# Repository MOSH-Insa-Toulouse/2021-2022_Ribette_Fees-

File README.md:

# 2021-2022_Ribette_Fees-
Projet capteur INSA Toulouse 2021-2022

# Sommaire
[1. A propos du projet](#A_propos)

[2. Circuit électronique](#Circuit_elec)

[3. Schématique et PCB KiCad](#Schem)

[4. Code Arduino](#Code)

[5. Application APK Bluetooth](#App)

[6. Banc de test](Banc)

[7. Datasheet](Sheet)

# 1. A propos du projet 

Ce répertoire comporte les différentes étapes effectuées pour le projet de l'UF "Du capteur au banc de test en open source hardware" proposé en 4ème année de Génie Physique de l'INSA Toulouse. Ce travail a été effectué par Antoine Fées et Mathis Ribette, sous la direction de M. Jérémie Grisolia, et avec l'aide de M. Biganzoli et Mme Crouzet, de l'INSA Toulouse. 

## 1.1 Prémices 

Les prémices de ce travail viennent d'un article scientifique,  _Pencil Drawn Strain Gauges and Chemiresistors on Paper, by Cheng-Wei Lin, Zhibo Zhao, Jaemyung Kim & Jiaxing Huang, Nature, published on January 22, 2014_ [1](https://www.nature.com/articles/srep03812), dans lequel est fabriqué un capteur de déformation à base d'une feuille de papier et d'un crayon à papier, avec une mine en graphite.. Le système granulaire que composent les particules de graphite étalées sur une feuille de papier par un crayon se comporte d'une manière intéressante : lorsque le papier est courbé, les particules de graphite se rapprochent ou s'éloignent, induisant une diminution ou une augmentation de la résistivité globale du "circuit électrique" ainsi créé. 

La grande difficulté vient de la résistivité de ce système, particulièrement élevée. Lorsqu'il est mélangé avec des molécules liantes pour qu'il soit moins friable, sa résistivité augmente fortement. Les crayons dans le commerce, des XB aux XH en passant par le standard HB, B pour les plus gras (bold) et H pour les plus durs (hard), avec X le niveau de gras ou de dureté associé (un 4B sera plus gras qu'un 2B et un 4H plus dur qu'un 2H), seront ceux que nous utiliserons. Dans cette classification, les plus gras comportent le plus de graphite et les plus durs le plus de molécules liantes. 
Cette différence de composition chimique et donc de dureté, est mise en évidence dans l'article par EDS _(energy dispersive spectroscopy)_, où les résultats suivants sont obtenus : 
- Plus on se rapproche du 9H, plus la proportion de liant est élevée. Les principaux éléments sont alors métalliques (Mg, Al) ou pseudo-métalliques (Si), avec également une forte teneur en oxygène. 
- A l'inverse, plus on se rapproche du 9B, plus la concentration en carbone augmente et plus celle des liants diminue.  

_Image ci-dessus : figure 2 de l'article : (a) EDS spectra of pencil leads correlating hardness with the fraction of carbon. Intensities of all of the spectra were normalized based on the carbon peak. (b–g) Optical microscopy images of traces drawn on the paper substrates from pencils of decreasing hardness._[1](https://www.nature.com/articles/srep03812)

## 1.2 Jauge de contrainte et graphite 

L'équipe de chercheurs a par la suite utilisé ces différents crayons et tracé des jauges de contraintes en forme de U sur des feuilles de papier. Ces jauges présentent une longueur de trait d'environ quelques centimètres pour une largeur de trait de quelques millimètres, comme le montre la figure 3 (a) de l'article ci-dessous. 
Le mécanisme de rapprochement ou d'éloignement des différents grains du système granulaire y est également représenté, (b-c-d).

_Image ci-dessus : figure 3 de l'article : (a) A photograph showing the U-shaped pencil trace drawn on a paper beam functioning as a strain gauge. (b) Schematic drawing shows that the number of connected graphite particle chains varies depending on the types of deformation. (c–d) Photograph of the gauge deformed by a single finger in compression and tension, respectively._[1](https://www.nature.com/articles/srep03812)

Les résistances obtenues sur ces dimensions par l'équipe de chercheurs sont alors les suivantes : 

| Crayon utilisé      | Résistance obtenue| 
| ------------- |:-------------:| 
| 9B     | 200 kOhms | 
| 6B     | 500 kOhms     | 
| 2B | 2 MOhms     |  
| HB | 20 MOhms |

Notons que l'article soutient que les résistances supérieures à 20 MOhms n'ont pas pu etre mesurées par l'équipe (un multimètre a été utilisé). Nous proposons alors de fabriquer un circuit électronique permettant de mesurer la variation de résistance relative à la déformation, afin d'obtenir un _flex sensor_ low-tech, open source et _user-friendly_. 

# 2. Circuit électronique 

Le circuit électronique que nous avons utilisé est un montage amplificateur à transimpédance, à amplificateur opérationnel. Afin de garantir une facilité d'utilisation, nous avons également ajouté un module Bluetooth qui nous permet, via une application réalisé avec le _MIT App Inventor_ de communiquer avec un téléphone portable android. Un potentiomètre digital commandé en SPI, monté en mode rhéostat à la place d'une résistance, nous permet de modifier le gain de l'amplificateur en temps réel. Nous avons également intégré un encodeur rotatoire, qui permet à l'utilisateur de faire des modifications en temps réel des actions du circuit, ainsi qu'un écran OLED qui affiche des informations utiles à l'utilisateur. Ce circuit électronique est monté sur PCB, puis monté sur un microcontroleur Arduino UNO. 

## 2.1 Choix du matériel 

Liste du matériel : 

| Fonction     | Référence| 
| ------------- |:-------------:| 
| Microcontroleur | Arduino UNO |
| Amplificateur opérationnel à faible bruit     | LTC 1050 | 
| Module Bluetooth     | HC05    | 
| Module encodeur rotatoire  | KY-040-GT055     | 
| Potentiomètre digital | MCP41050 |
| Résistances | 270k, 100k, 10k, 33 ohms ...|
| Capacités | 100pF, 10uF ...|

## 2.2 Schématisation du circuit électronique et modifications apportées

Une représentation 3D de notre PCB est visualisable sur les images ci-dessous, issues du logiciel Kicad : 

Un schéma LTSpice du matériel est visible sur l'image ci-dessous, qui est fidèle au circuit tel que fabriqué sur le PCB. Par la suite cependant, nous introduirons plusieurs manières différentes de représenter notre _flex sensor_, notamment afin de tester l'impact du bruit :

La résistance {Rsensor} étant le _flex sensor_ et la résistance Rvar étant le potentiomètre digital, monté en série avec une résistance de 33 Ohms. La sortie Vout est reliée à une entrée analogique du CAN du microcontroleur arduino, qui traitera la donnée analogique brute afin d'en extraire des informations. 
Une analyse électrique du schéma précédent donne : 

- V+ = E*(R1//C1)/(Rsens+R5+(R1//C1))
- V- = Vout/(1+((R3//C4)+R6)/(R2+Rvar))
- **Vout = E(R1//C1)(1+((R3//C4)+R6)/(R2+Rvar))/(Rsens+R5+(R1//C1)**
, où E=5V. 

On remarque que :

• R5 en entrée protège l'ampli opérationnel contre les décharges électrostatiques, et
forme avec C1 un filtre pour les bruits en tension
• C1 et R1 forment un filtre pour le bruit en courant
• R2 est adaptable avec le potentiomètre digital, pour changer le calibre
• C4 et R3 forment un filtre actif
• C2 et R6 forment le filtre de sortie
• C3 filtre le bruit d'alimentation

Dans notre cas, la seule modification permanente est l'ajout d'un potentiomètre digital dont la résistance varie entre 500 Ohms et 51800 Ohms environ, et le remplacement de R3 par une résistance plus élevée (270 kOhms) afin d'augmenter le gain possible par notre montage. En effet, comme nous l'avons vu avec la formule précedente, la tension de sortie est à peu près proportionnelle à 1+R3/Rvar et donc augmenter R3 nous permet d'augmenter le gain. Le potentiomètre digital est commandé sur 8 bits et donc peut prendre 256 valeurs de résistance régulièrement espacées, environ de 200 Ohms les unes des autres. Le milieu de cette plage de fonctionnement étant environ à 25 kOhms, nous avons décidé d'augmenter R3 afin d'avoir, en conditions "nominales" un gain d'environ 11. Rappelons que le gain conseillé était de 100. Il nous est possible d'arriver à cette valeur de gain, mais il faut pour cela imposer une résistance d'environ 2,7kOhms au potentiomètre digital, ce qui n'arrive qu'à environ le dixième de sa plage utilsable. Une solution, afin de toujours repousser les limites de ce gain, est d'augmenter la valeur de R3 et diminuer celle de Rvar, mais on se heuret à d'autre problèmes rencontrés lorsque les résistances sont très élevées.  

Une autre solution, plus couteuse, serait d'adjoindre un étage amplificateur inverseur à la suite d'un amplificateur transimpédance : nous n'aurions pas besoin de résistances élevées. 

## 2.3 Test de la validité du modèle électrique 

Testons notre formule pour le gain. En utilisant la formule **Vout = E(R1//C1)(1+((R3//C4)+R6)/(R2+Rvar))/(Rsens+R5+(R1//C1)** sur excel, on obtient : 

De l'autre coté, une analyse effectuée de la meme manière avec le logiciel spice donne la courbe ci-dessous, où on voit la tension de sortie Vout en fonction de la résistance du capteur pour différentes valeurs de résistance imposées par le potentiomètre digital. 

Où les instructions données sont : 
- **.step param Rvar 1k 51k 10k**
- **.step param Rsensor 1000k 20000k 1000k**
- **.op**

Ces instructions ordonnent au logiciel SPICE de calculer l'**operating point**, le point d'équilibre du circuit et sa valeur de tension de sortie associée. Nous remarquons les memes courbes que pour le calcul excel : la fonction de transfert écrite ci-dessus semble correcte. Au-delà de cela, on remarque que des valeurs précises de résistances imposées par le potentiomètre digital sont nécessaires pour garder la tension de sortie *Vout* dans une fourchette facilement utilisable par l'entrée analogique du microcontroleur arduino. Nous verrons plus tard qu'une solution de réglage automatique du gain a été mise en oeuvre et testée, et les résultats qu'elle produit. 
Nous remarquons que les variations de tensions de sortie ne répondent pas linéairement aux variations de résistance du capteur. En particulier, deux problèmes se posent : 

- Pour des résistances faibles et des gains forts, la tension de sortie dépasse rapidement les 5V et le capteur sature. Cet effet devient prégnant pour des résistances de valeurs faibles (inférieures au MOhm) et la résistance du potentiomètre digital faible également. Un réglage du potentiomètre digital à de très grandes valeurs de résistance permet de contourner ce problème en diminuant le gain. 
- Pour des résistances de capteur élevées et des gains forts, on remarque un aplatissement de la courbe, *i.e.* une variation importante de résistance du capteur (une déformation importante) s'accompagne d'une variation faible de tension de sortie Vout. Cela pose un problème du à la mesurabilité d'une variation de tension, qui n'est pas assurée pour des variations faibles. Rappelons que le quantum de variation pour un microcontroleur Arduino UNO avec un *CAN* de 10bits est d'environ 5mV (5mV/2^10 = 4,88 mV). Des variations inférieures à 5mV ne sont donc pas mesurables, d'autant plus que du bruit apparait et augmente encore la difficulté de la mesure. 
- Un troisème problème est celui de la précision du potentiomètre digital. Un bref calcul indique que 200 ohms d'écart entre deux valeurs de Rvar impose une différence de G = (1+(R3+R6)/(R2+Rvar)) de 0,09 environ à Rvar = 25k, et 8,09 environ à Rvar = 2,5k, soit respectivement 0,74% et 7,8% du gain. Cette différence n'est pas négligeable et doit etre prise en compte lors de la détermination de la mesure. En somme, on essaiera au maximum de se placer dans une zone où cette différence à le moins d'impact, donc à des gains plus faibles. 

1) Conditions nominales d'utilisation. 

En somme, **plus la résistance du capteur augmente, plus ses variations deviennent difficiles à mesurer**. Ces éléments nous permettent de répondre à la première question, celle de tester les **conditions nominales** du capteur. 
Afin de garantir une mesure plus ou moins précise, la condition nominale d'utilisation du capteur sera dans une plage de résistannces de **1 à 10 MOhms** environ. Au-delà, il deviendra impossible d'ajuster en temps réel la valeur du potentiomètre digital avec suffisamment de précision pour ne pas compromettre la mesure. Il sera donc nécessaire de fixer sa valeur. La limite sera alors les 5mV de quantum de variation détectable par l'Arduino, et évidemment, le bruit qui subsistera. 
Un test empirique sur des résistances connues, de 1 et 10 MOhm, nous a permis de nous convaincre de la précision de la mesure, et de raisonnablement croire à la validité de cette plage de résistances. 

2) Influence de l'*offset voltage* imposé par l'amplificateur LTC1050

Une analyse sur Spice de l'offset existant imposé par l'amplifacteur LTC1050 permet d'estimer son effet. En agissant à tension différentielle nulle, l'amplificateur impose un offset qui se propage jusqu'à la tension Vout. Cet effet, implémenté sur Spice, nous permet de raisonner sur la viabilité du montage. 

On remarque des tensions d'offset dépendant de la résistance variable Rvar. Ces tensions d'offset sont relativement importantes, de 100 à 200mV. Examinons, à Rvar constante, l'impact d'une variation de tension dV, à basse fréquence. On constate : 

*Figure ci-dessus : Tension de sortie en entrée court-circuitée en fonction de la valeur de la résistance variable* 

Soit :
- Rsensor = (E.R1.(1+R3+R6)./(Vout.(R2+Rvar)))-R5-R1
- E=5V
On a alors :
- dR/Rsensor(dV,Vout)= (Rsensor(Vout + dV)-Rsensor(Vout))/Rsensor(Vout) = A*(1-Vout/(Vout+dV))/(A-Vout.(R5+R1))
- avec A=E.R1.(1+R3+R6)/(R2+Rvar) 

Plusieurs dV sont possibles :
- dV = 5/1023 V (pas de quantification) 
- dV correspondant à l'offset, dépendant de Rvar 

On constate une erreur d'offset très importante par rapport à l'erreur de quantification. On a également une variabilité importante de cet offset par rapport à la résistance du potentiomètre digital en mode rhéostat. En somme, si elle est négligeable pour l'utilisation du capteur dans une large plage de tensions, pour une meme résistance, le passage d'une résistance à une autre est à controler. 

# 3. Schématique et PCB KiCad 

La réalisation du PCB a demandé plusieurs étapes de conception, allant de la schématique jusqu'à la soudure, en passant par le tracé des pistes sur la carte. Nous allons maintenant détailler le fruit de notre travail sur cette partie.

## 3.1 Symboles, empreintes et schématique

Voici les symboles et empreintes réalisés pour les différents éléments composant notre PCB :

* Encodeur rotatoire

* Ecran OLED

* Module Bluetooth HC-05

* Potentiomètre 

* Amplificateur opérationnel LTC 1050

Et voici la schématique complète de notre circuit, ainsi que les correspondances entre les PINS des composants et de l'Arduino :

## 3.2 Réalisation des pistes et placement des composants

C'est cette étape qui nous a demandé le plus de temps et d'attention. En effet, nous avons eu quelques difficultés à relier les PINS de manière satisfaisante et pour cela nous avons fait appel à deux vias.

Nous avons fait appel à la visualisation 3D pour vérifier que les composants se plaçaient bien et n'entraient pas en conflit.

Malheureusement, nous n'avions pas prévu que l'encodeur rotatoire et le module Bluetooth soient placés sur des headers courbés, ce qui représentera un problème par la suite.

## 3.3 Fabrication du SHIELD

Nous avons fabriqué notre PCB sur une plaque d'epoxy protégée par une couche fine de cuivre. Pour cela, nous avons imprimé notre PCB sur un calque pour qu'ensuite, à l'aide d'une insolation UV, l'empreinte soit reproduite sur notre plaque et jouant le rôle d'une résine protectrice. Puis, nous avons placé notre plaque dans une solution de perchlorure de fer. Ainsi, le cuivre non recouvert de résine est éliminé et nous obtenons notre PCB.
Ensuite, nous avons percé (1mm pour les headers et connecteurs de l'Arduino et 8mm pour le reste) et soudé les éléments composant notre PCB.
C'est à cette étape que nous nous sommes rendus compte du problème de l'encodeur et du module Bluetooth et avons donc coupé les pattes de l'encodeur pour le soûder dans l'autre sens, et ainsi avoir la place de le placer sur le PCB.
Aussi, nous avons réalisé avoir inversé les PINS SDA et SCL de l'OLED sur l'Arduino et donc avons corrigé cela.

# 4. Code Arduino 

Dans cette partie, est détaillé le code Arduino utilisé pour mener à bien le projet. Le code est intégralement retranscrit, et également sous forme de logigramme. 

## 4.1 Structure générale 

La structure générale est comme suit : 
- Une partie de déclaration de variables globales et de définitions
- Une partie de Setup (code qui ne s'exécute qu'une fois) 
- Une partie Loop qui s'exécute en boucle 

*figure ci-dessus : schéma récapitulatif de la structure du code Arduino* 

Egalement, sont présents des fonctions supplémentaires (d'interruption par exemple). Nous y viendrons ultérieurement. 

## 4.2 Déclaration de variables globales, définitions 

La première partie est donc une partie de déclaration de variables, et de définitions qui seront utiles dans le Loop et dans le Setup. Nous appellons cette partie le PRE-SETUP. La structure de notre code est : 

*figure ci-dessus : schéma récapitulatif de la structure de notre code PRE-SETUP. 
*- Variables globales : Résistances, Pins ... 
*- Définitions : libraires, fichiers à utiliser 

Les deux images ci-dessus rassemblent les éléments précédemment cités. Chaque utilité est brièvement rappelée en commentaire (//). 

## 4.3 Setup 

Le setup est organisé comme suit : 

Le code associé est le suivant : 

## 4.4 Loop 

La troisième partie du code est le loop, la partie du code qui re-boucle sans arret, et est juste arretée momentanément par les interruptions; ici la fonction d'interruption doEncoder utilisée pour l'encodeur rotatoire (en bleu sur le schéma ci-dessus). 

Structure du loop : 

### 4.4.1 Ajustement proportionnel du gain 

La structure *void loop* commence avec l'ajustement proportionnel du gain de notre montage amplificateur pour obtenir une tension de 2,5 V en guise de Vout. Cette adaptation nous permet de rester dans une plage d'utilisation convenable. Elle fonctionne en augmentant ou diminuant la valeur de consigne (entre 0 et 255) donnée au potentiomètre digital et donc respectivement diminuer ou augmenter la résistance, respectivement diminuant ou augmentant le gain du montage.
Bien évidemment, nous avons fait en sorte que la valeur de consigne envoyée au potentiomètre digital reste entre 0 et 255 compris; pour ne pas poser de problèmes. 
Enfin, la résistance actuelle de R2, ajustée, nous permet de calculer la véritable valeur de résistance du capteur Rs. Avec cette méthode, nous avons une valeur qui se stabilise rapidement autour de la valeur réelle de résistance souhaitée tout en s'assurant que la tension à l'entrée du convertisseur analogique numérique de l'arduino reste autour de 2,5V. 

Afin d'augmenter la vitesse de réponse, nous avons implémenté une correction proportionnelle de la position du wiper de l'encodeur rotatoire. dV, la différence de tension entre les 2,5V de consigne (Vconsigne) et la tension effectivement mesurée analgoRead(PotPin) (Vmesuré), est multipliée par un coefficient (5,0), puis convertie en entier et c'est de cette valeur qu'est augmentée ou diminuée la position du wiper. En somme, au lieu de faire un déplacement incrémental unique de la position du wiper, ou meme de faire un déplacement important mais toujours constant de la position du wiper, le système adapte le déplacement à la valeur souhaitée, résultant en un système beaucoup plus rapide. 

Ci-dessous un schéma qui récapitule le fonctionnement de notre code : 

Le code associé est : 

### 4.4.2 Lecture de la valeur de tension 

Afin que la boucle correctrice fonctionne, et que la valeur de résistance lue puisse varier, on vient lire à chaque tour de boucle la tension en sortie du montage amplificateur, puis transformer cette valeure en valeur de résistance (avec la formule du gain précedemment énoncée). Le code est : 

La valeur de R2 varie à chaque tour de boucle en raison de l'action stabilisatrice de la résistance du potentiomètre digital, et la valeur de Vadc varie à chaque tour en conséquence (et une mesure est effectuée à chaque tour). La valeur de Rs se stabilise donc autour de la valeur vraie. 

### 4.4.3 Interruption de la boucle LOOP & debouncing associé : encodeur rotatoire 

Une interruption de la boucle loop est effectuée lorsqu'un changement de la valeur de l'encodeur rotatoire est détecté sur le pin d'interruption du microcontroleur. Cette interruption est agrémentée d'un *debouncing*, c'est-à-dire que les variations lues par le microcontroleur ne sont prises en compte que si elles sont suffisamment espacées les unes des autres. 

Ici, la fonction d'interruption lit un temps, regarde si ce temps est assez éloigné du temps de la dernière interruption (>150ms). Si c'est le cas, la fonction remplit sa mission (elle change la valeur du Scale pour l'envoi de la donnée vers le module Bluetooth et l'application APK). Si ce n'est pas le cas, la fonction ne fait rien et le programme repart dans la boucle LOOP, mettant fin *de facto* à l'interruption. Cette fin d'interruption s'accompagne d'une mesure du temps, afin de mettre à jour la date de la dernière interruption qui sert à la comparaison. Le système de debouncing ainsi crée permet de se débarrasser des changements intempestifs lus par le pin arduino dus au bruit. Ce système est réglé par défaut à 150 ms de temps, mais il serait possible de changer cette valeur. 

Ci-dessous un schéma récapitulatif de cette fonction : 

Et le code associé :

Comme vous pouvez le voir, cette fonction d'interruption change la valeur de la variable *Scale* qui permet de faire un *mapping* de la valeur de résistance envoyée à l'application APK vie Bluetooth (c'est à dire de choisir de contraintre l'envoi de la donnée dans certaines limites, changeant ainsi le "zoom" de la donnée autour d'une valeur particulière, ici définie à 5 MOhm). 

### 4.4.4 Mapping de la donnée et envoi à l'application Bluetooth

Dans le code suivant, la donnée, comprise entre 0 et 10 000 (unité kOhm), est envoyée en la centrant autour de 5 000 (kOhm) en fonction de la valeur du Scale, via la fonction constrain(), vers un entier compris entre 0 et 127. 

- Si la résistance varie beaucoup, l'utilisateur peut choisir de placer la variable Scale à 1 (en tournant l'encodeur rotatoire dans le sens horaire pour augmenter la valeur de scale, antihoraire pour la diminuer) et ainsi profiter d'une plage allant de 0 à 10 000 (kOhm). 
- Si la variation est plus faible au contraire, la valeur de résistance est contrainte dans un intervalle plus faible (entre 4000 et 6000 kOhm si Scale est à 5 par exemple). 

La valeur ainsi obtenue est donc plus ou moins zoomée sur l'application APK : la valeur envoyée est toujours comprise entre 0 et 127 (conformément aux egigences de l'application) mais les limites inférieure et supérieures correspondent à des résistances plus ou moins espacées (d'une plage de 10MOhm à 1Mohm). 

Le code qui y est associé est : 

La valeur de la variable scale ainsi choisie permet donc de contraindre la donnée et de l'envoyer sous un format utilisable par l'application, avec le code suivant : 

### 4.4.5 Affichage sur l'écran OLED des informations 

Ensuite, on affiche les différentes valeurs utiles sur l'écran OLED :
- la résistance, convertie en kOhm, 
- la valeur de position du wiper du potentiomètre digital, comprise entre 0 et 255 
- la valeur de la variable *scale* et donc le zoom effectif de l'affichage sur l'application APK

Le code est :

Enfin, un délai de 300 ms entre deux tours de boucle LOOP est pris. 

# 5. Application APK Bluetooth 

Nous avons réalisé une application Android recevant les données de résistance de notre capteur via le module Bluetooth HC-05, qui affiche les données et trace le graphique de l'évolution de la résistance en fonction du temps. Pour cette dernière fonctionnalité, nous avons réalisé un mapping de la mesure dans le code Arduino.

# 6. Banc de test 

Pour tester notre capteur et réaliser sa datasheet, nous avons réfléchi à plusieurs protocoles. Cependant, seulement un nous a permis d'obtenir des résultats cohérents. 
Nous avons fabriqué différents capteurs avec des sections différentes à l'aide d'un crayon HB comme ceci :

Ensuite, nous avons inséré notre capteur dans des cercles en papier avec des rayons différents, pour que notre capteur subisse des compressions avec des rayons de courbure différents : 

Nous avons ainsi pu effectuer plusieurs mesures de résistance en fonction du rayon de courbure et tracer son évolution en fonction du rayon : 

On observe bien que l'écart relatif de la résistance diminue avec l'augmentation du rayon de courbure, et donc que plus le capteur est comprimé, plus la résistance est faible.
Nous avons aussi réalisé des capteurs avec un crayon 2H, mais nous n'avons pas obtenu de résultats cohérents, les résistances à mesurer étant bien plus supérieures à la plage de mesure de notre capteur (1 - 10 Mohm).

# 7. Datasheet 

La datasheet précise les caractéristiques de notre capteur ainsi que son environnement et son utilisation.

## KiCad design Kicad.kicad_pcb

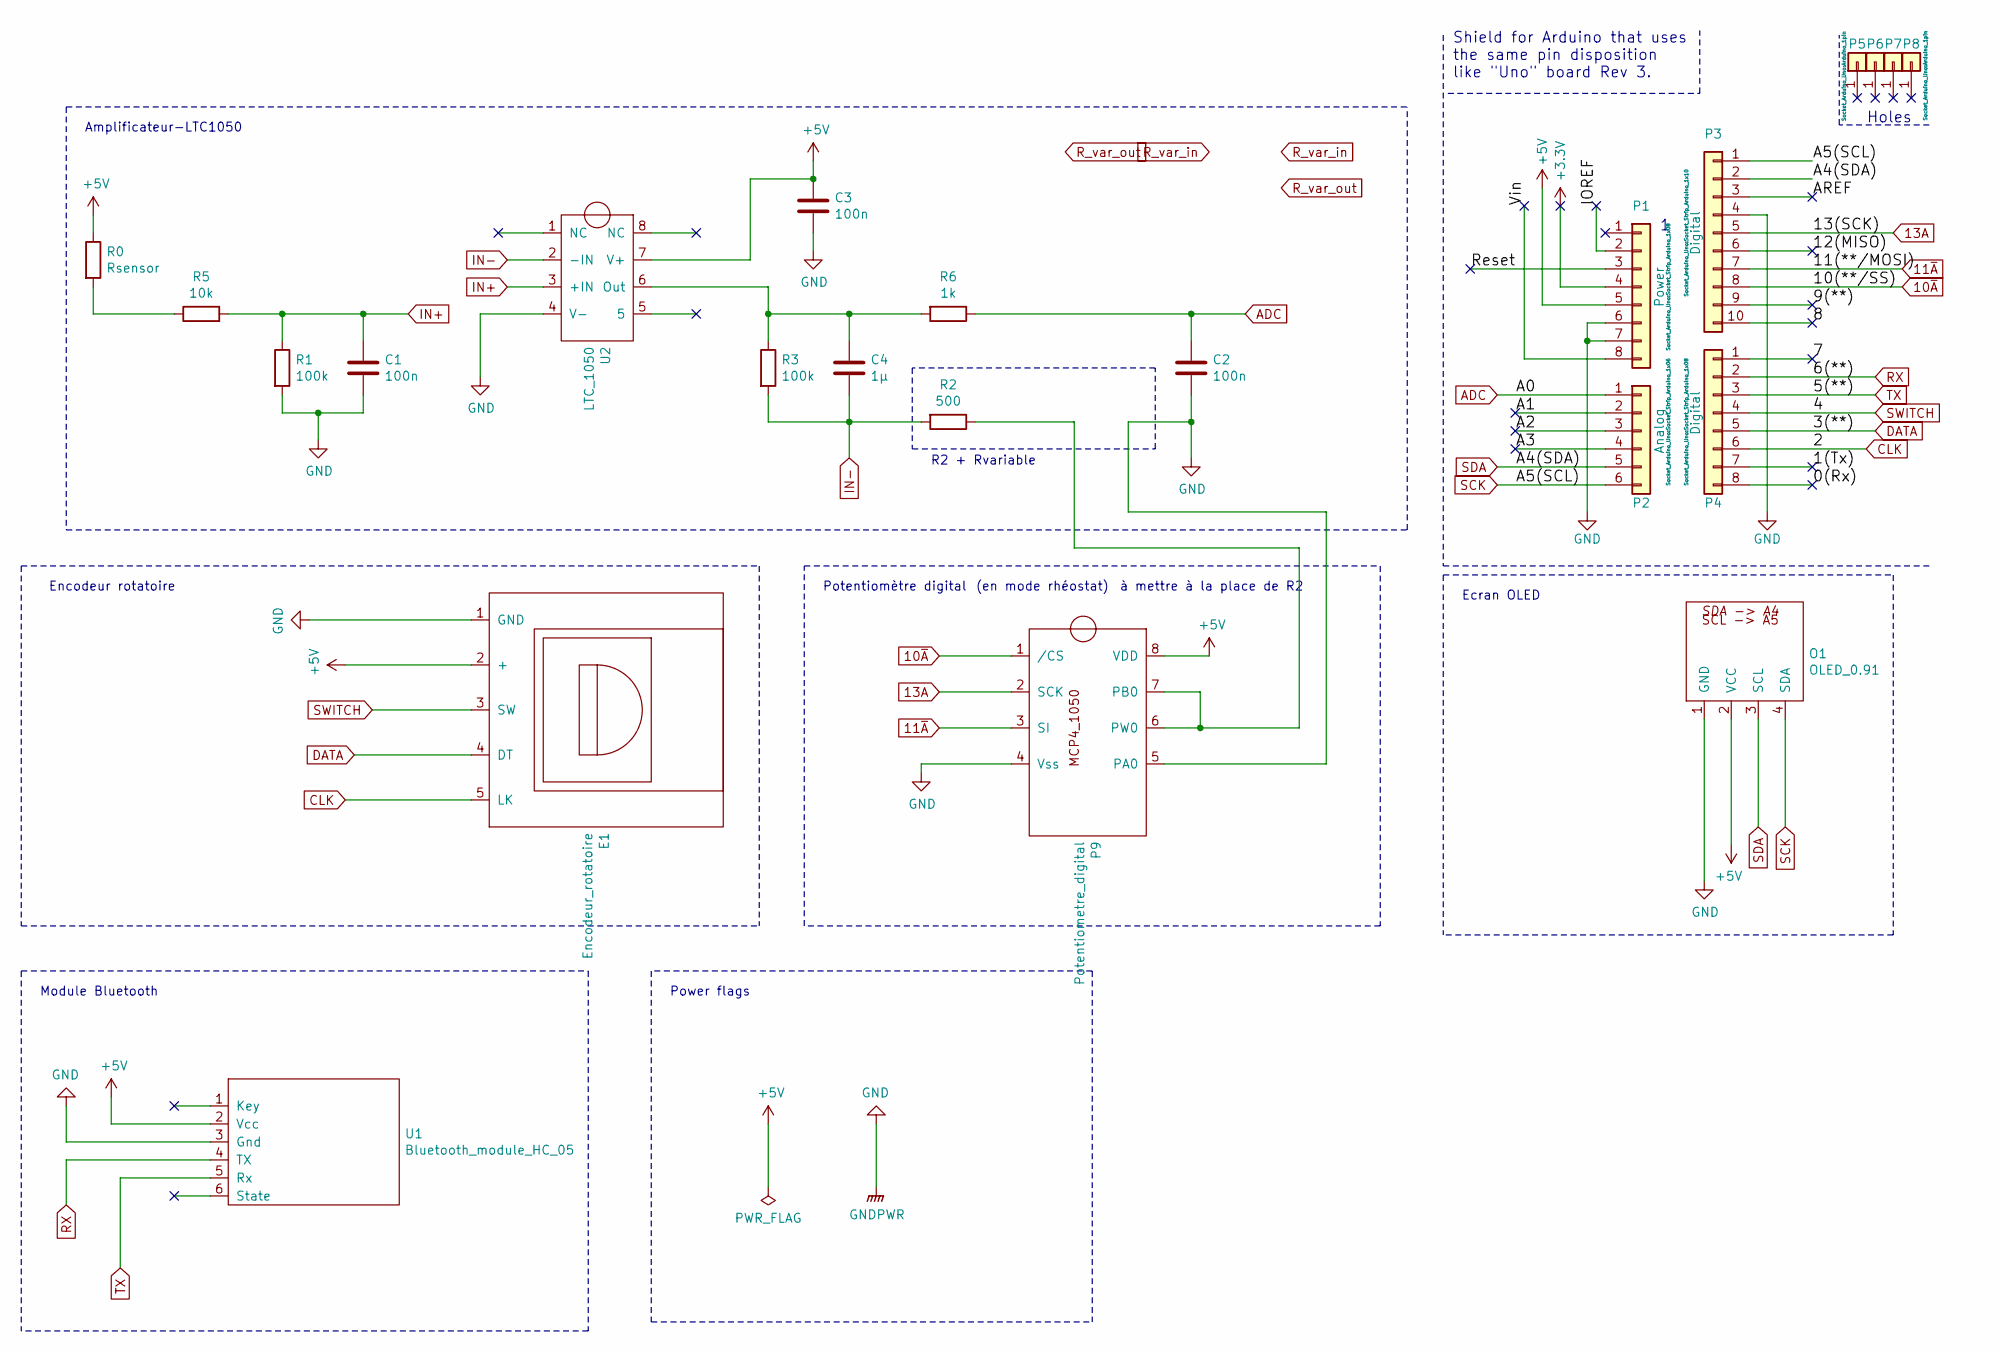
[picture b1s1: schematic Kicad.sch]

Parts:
C1, C2, C3: 100n; C_Disc_D7.5mm_W5.0mm_P5.00mm
C4: 1µ; C_Rect_L7.5mm_W6.5mm_P5.00mm
E1: Encodeur_rotatoire; SIP-5
O1: OLED_0.91; SIP-4
P1: Power; Socket_Strip_Arduino_1x08
P2: Analog; Socket_Strip_Arduino_1x06
P3: Digital; Socket_Strip_Arduino_1x10
P4: Digital; Socket_Strip_Arduino_1x08
P5, P6, P7, P8: CONN_01X01; Arduino_1pin
P9: Potentiometre_digital; potentiometre_digital
R0: Rsensor; R_Axial_DIN0204_L3.6mm_D1.6mm_P5.08mm_Horizontal
R1, R3: 100k; R_Axial_DIN0204_L3.6mm_D1.6mm_P5.08mm_Horizontal
R2: 500; R_Axial_DIN0204_L3.6mm_D1.6mm_P5.08mm_Horizontal
R5: 10k; R_Axial_DIN0204_L3.6mm_D1.6mm_P5.08mm_Horizontal
R6: 1k; R_Axial_DIN0204_L3.6mm_D1.6mm_P5.08mm_Horizontal
U1: Bluetooth_module_HC_05; hc05
U2: LTC_1050

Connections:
10~A: P3.8, P9.1 (/CS)
11~A: P3.7, P9.3 (SI)
13A: P3.5, P9.2 (SCK)
+3V3: P1.4
+5V: C3.1, E1.2 (+), O1.2 (VCC), P1.5, P9.8 (VDD), R0.1, U1.2 (Vcc), U2.7 (V+)
/0(Rx): P4.8
/1(Tx): P4.7
/7: P4.1
/8: P3.10
/9(**): P3.9
/12(MISO): P3.6
/A1: P2.2
/A2: P2.3
/A3: P2.4
/AREF: P3.3
/IOREF: P1.2
/Reset: P1.3
/Vin: P1.8
ADC: C2.1, P2.1, R6.1
CLK: E1.5 (LK), P4.6
DATA: E1.4 (DT), P4.5
GND: C1.2, C2.2, C3.2, E1.1 (GND), O1.1 (GND), P1.6, P1.7, P3.4, P9.4 (Vss), P9.5 (PA0), R1.2, U1.3 (Gnd), U2.4 (V-)
IN+: C1.1, R1.1, R5.2, U2.3 (+IN)
IN-: C4.2, R2.2, R3.2, U2.2 (-IN)
unnamed: C4.1, R3.1, R6.2, U2.6 (Out)
unnamed: P9.6 (PW0), P9.7 (PB0), R2.1
unnamed: R0.2, R5.1
RX: P4.2, U1.4 (TX)
SCK: O1.4 (SDA), P2.6, P3.1
SDA: O1.3 (SCL), P2.5, P3.2
SWITCH: E1.3 (SW), P4.4
TX: P4.3, U1.5 (Rx)

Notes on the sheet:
Holes
Shield for Arduino that uses the same pin disposition like "Uno" board Rev 3.
Amplificateur-LTC1050
Module Bluetooth
Potentiomètre digital
(en mode rhéostat)
à mettre à la place de R2
Ecran OLED
Power flags
R2 + Rvariable
Encodeur rotatoire

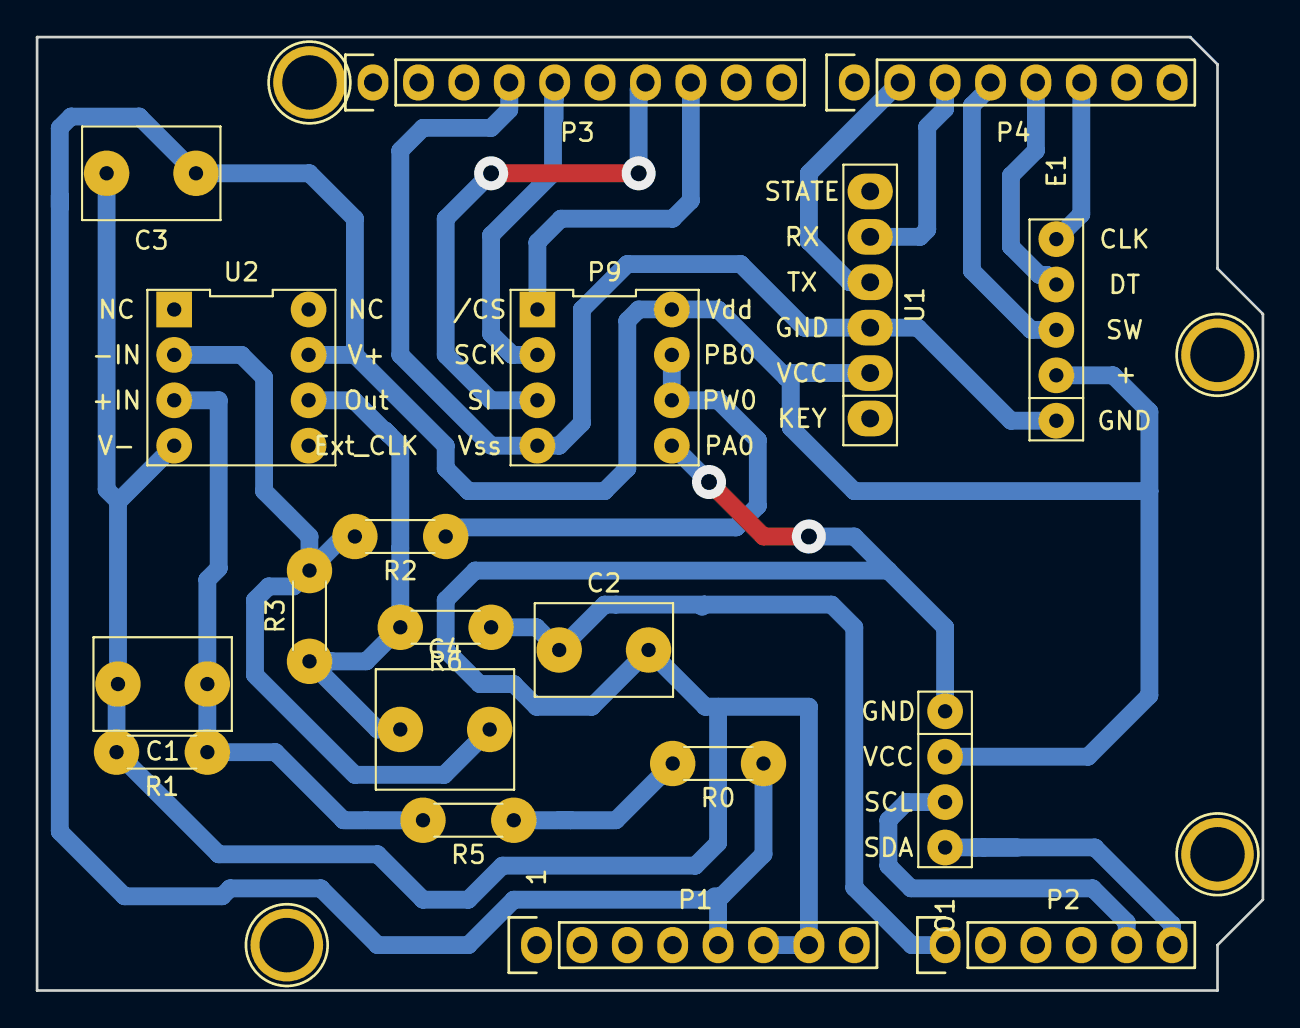
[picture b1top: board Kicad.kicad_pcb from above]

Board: 2 copper layers, 68.6 x 53.3 mm, 23 parts (0 on the bottom side), 18 nets.
